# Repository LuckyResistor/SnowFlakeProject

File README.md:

# The Snowflake Decoration Project

This repository contains all hardware and software sources for the snowflake decoration project.
You will also find a number of documentation pages with the wiring or arrangement of the LEDs.

## More Information

Find more information about the project here:
[Snowflake Decoration Project](https://luckyresistor.me/projects/snow-flake-decoration/)

## License

All files are licensed under the GNU General Public License v3.0.

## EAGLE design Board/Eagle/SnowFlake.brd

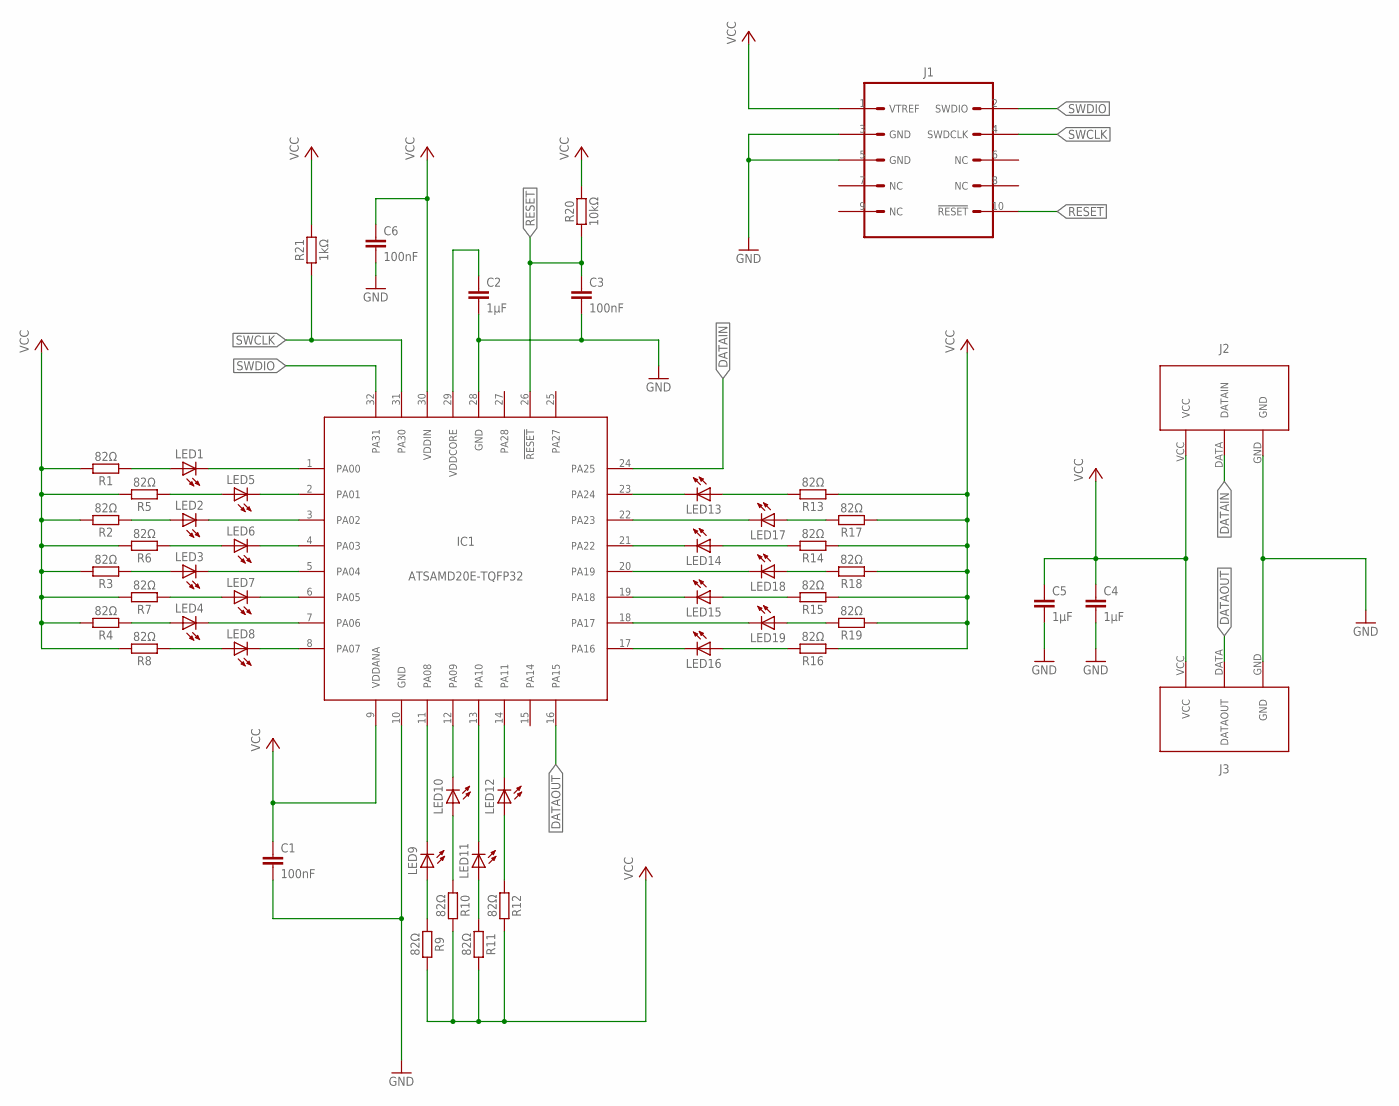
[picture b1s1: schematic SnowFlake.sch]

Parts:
C1, C3, C6: 100nF; CAPACITOR-0805-MURATA-GRM-21
C2, C4, C5: 1µF; CAPACITOR-0805-MURATA-GRM-21
IC1: ATSAMD20E-TQFP32; TQFP32-08
J1: CON-CORTEX-DEBUG-SMD1.27; CON-2X5-HARWIN-1.27
J2: CON-SNOWF-IN; CON-PADS-3XWIRE-B
J3: CON-SNOWF-OUT; CON-PADS-3XWIRE-T
LED1, LED2, LED3, LED4, LED5, LED6, LED7, LED8, LED9, LED10, LED11, LED12, LED13, LED14, LED15, LED16, LED17, LED18, LED19: LED0402; LED-0402-ROHM
R1, R2, R3, R4, R5, R6, R7, R8, R9, R10, R11, R12, R13, R14, R15, R16, R17, R18, R19: 82Ω; RESISTOR-0805-KOA-RK73-2A
R20: 10kΩ; RESISTOR-0805-KOA-RK73-2A
R21: 1kΩ; RESISTOR-0805-KOA-RK73-2A

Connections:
DATAIN: IC1.24 (PA25), J2.DATA (DATAIN)
DATAOUT: IC1.16 (PA15), J3.DATA (DATAOUT)
GND: C1.2, C2.2, C3.2, C4.2, C5.2, C6.2, IC1.10 (GND), IC1.28 (GND), J1.3 (GND), J1.5 (GND), J2.GND, J3.GND
LED1P: LED1.A, R1.1
LED1S: IC1.1 (PA00), LED1.C
LED2P: LED2.A, R2.1
LED2S: IC1.3 (PA02), LED2.C
LED3P: LED3.A, R3.1
LED3S: IC1.5 (PA04), LED3.C
LED4P: LED4.A, R4.1
LED4S: IC1.7 (PA06), LED4.C
LED5P: LED5.A, R5.1
LED5S: IC1.2 (PA01), LED5.C
LED6P: LED6.A, R6.1
LED6S: IC1.4 (PA03), LED6.C
LED7P: LED7.A, R7.1
LED7S: IC1.6 (PA05), LED7.C
LED8P: LED8.A, R8.1
LED8S: IC1.8 (PA07), LED8.C
LED9P: LED9.A, R9.1
LED9S: IC1.11 (PA08), LED9.C
LED10P: LED10.A, R10.1
LED10S: IC1.12 (PA09), LED10.C
LED11P: LED11.A, R11.1
LED11S: IC1.13 (PA10), LED11.C
LED12P: LED12.A, R12.1
LED12S: IC1.14 (PA11), LED12.C
LED13P: LED13.A, R13.2
LED13S: IC1.23 (PA24), LED13.C
LED14P: LED14.A, R14.2
LED14S: IC1.21 (PA22), LED14.C
LED15P: LED15.A, R15.2
LED15S: IC1.19 (PA18), LED15.C
LED16P: LED16.A, R16.2
LED16S: IC1.17 (PA16), LED16.C
LED17P: LED17.A, R17.2
LED17S: IC1.22 (PA23), LED17.C
LED18P: LED18.A, R18.2
LED18S: IC1.20 (PA19), LED18.C
LED19P: LED19.A, R19.2
LED19S: IC1.18 (PA17), LED19.C
RESET: C3.1, IC1.26 (!RESET), J1.10 (!RESET), R20.1
SWCLK: IC1.31 (PA30), J1.4 (SWDCLK), R21.1
SWDIO: IC1.32 (PA31), J1.2 (SWDIO)
VCC: C1.1, C4.1, C5.1, C6.1, IC1.9 (VDDANA), IC1.30 (VDDIN), J1.1 (VTREF), J2.VCC, J3.VCC, R1.2, R2.2, R3.2, R4.2, R5.2, R6.2, R7.2, R8.2, R9.2, R10.2, R11.2, R12.2, R13.1, R14.1, R15.1, R16.1, R17.1, R18.1, R19.1, R20.2, R21.2
VDDCORE: C2.1, IC1.29 (VDDCORE)

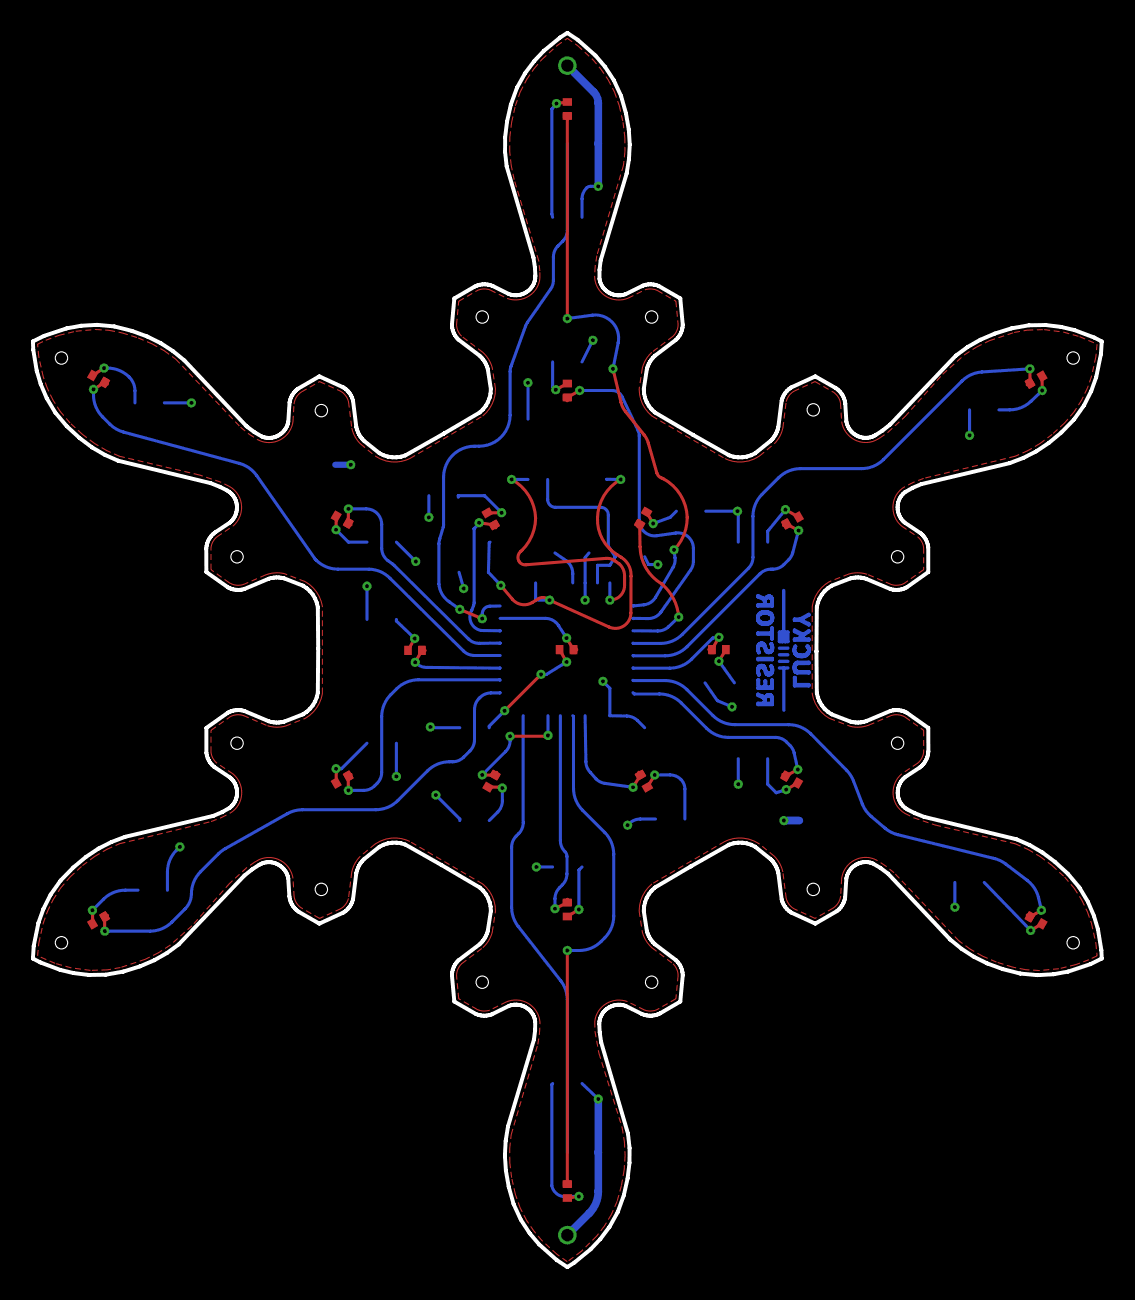
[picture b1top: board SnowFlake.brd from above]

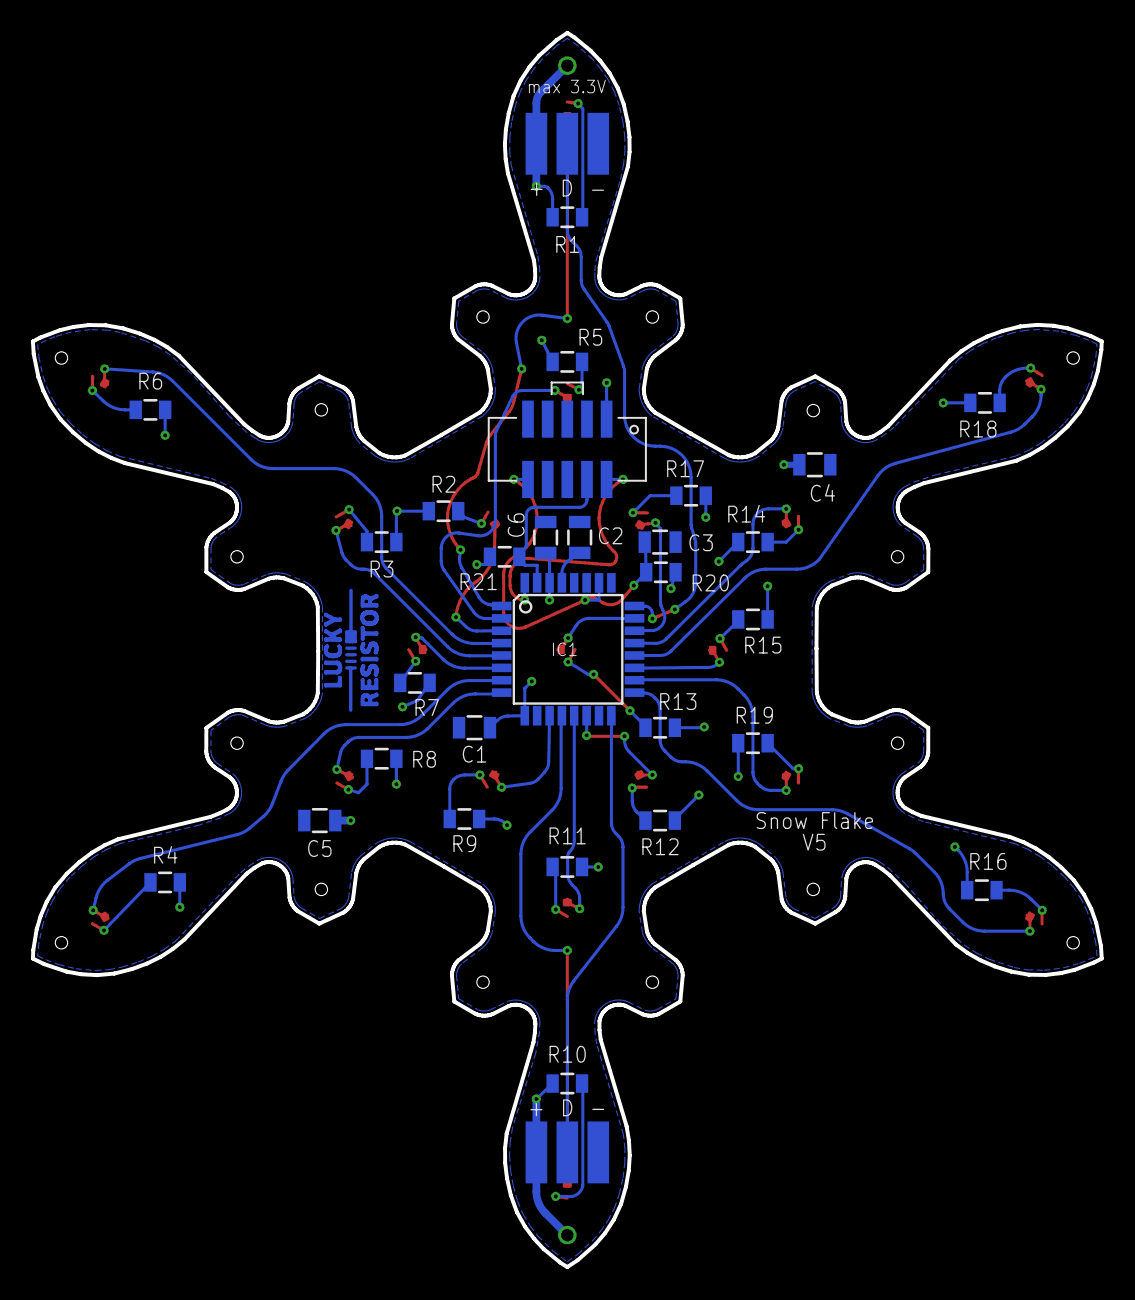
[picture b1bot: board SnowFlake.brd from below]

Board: 2 copper layers, 69.1 x 79.8 mm, 51 parts (32 on the bottom side), 46 nets.

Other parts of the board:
U$1: LR_LOGO_COPPER_8MM

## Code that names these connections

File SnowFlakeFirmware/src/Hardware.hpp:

//
// Snow Flake Project
// ---------------------------------------------------------------------------
// (c)2017 by Lucky Resistor. See LICENSE for details.
// https://luckyresistor.me
//
// This program is free software; you can redistribute it and/or modify
// it under the terms of the GNU General Public License as published by
// the Free Software Foundation; either version 2 of the License, or
// (at your option) any later version.
//
// This program is distributed in the hope that it will be useful,
// but WITHOUT ANY WARRANTY; without even the implied warranty of
// MERCHANTABILITY or FITNESS FOR A PARTICULAR PURPOSE.  See the
// GNU General Public License for more details.
//
// You should have received a copy of the GNU General Public License along
// with this program; if not, write to the Free Software Foundation, Inc.,
// 51 Franklin Street, Fifth Floor, Boston, MA 02110-1301 USA.
//
#pragma once


#include <cstdint>


/// The hardware abstraction layer.
///
namespace Hardware {


/// The port.
///
enum class PortName : uint8_t {
	PA00 = 0,
	PA01 = 1,
	PA02 = 2,
	PA03 = 3,
	PA04 = 4,
	PA05 = 5,
	PA06 = 6,
	PA07 = 7,
	PA08 = 8,
	PA09 = 9,
	PA10 = 10,
	PA11 = 11,
	PA14 = 14,
	PA15 = 15,
	PA16 = 16,
	PA17 = 17,
	PA18 = 18,
	PA19 = 19,
	PA22 = 22,
	PA23 = 23,
	PA24 = 24,
	PA25 = 25,
	PA27 = 27,
	PA28 = 28,
	PA30 = 30,
	PA31 = 31,
};


/// The multiplexing function.
///
enum class Multiplexing : uint8_t {
	Off, ///< Do not connect to any peripheral.
	A, ///< Connect to external interrupt.
	B, ///< Connect to analog input (REF, ADC, AC, PTC, DAC).
	C, ///< Connect to SERCOM.
	D, ///< Connect to SERCOM-ALT.
	E, ///< Connect to timer (TC).
	G, ///< Connect to COM.
	H, ///< Connect to Generic Clock.
};

/// Port Configuration.
///
enum class PortConfiguration : uint8_t {
	Disabled, ///< Remove the port from the GPIO (Hi-Z)
	Output, ///< Configure the port as output.
	Input, ///< Configure the port as input.
};

/// Pull up/down.
///
enum class PortPull : uint8_t {
	None, ///< Use no pull up/down resistor.
	Up, ///< Connect a pull up resistor.
	Down ///< Connect a pull down resistor.
};

/// The port state.
///
enum class PortState : uint8_t {
	Low, ///< Set the port to high state.
	High ///< Set the port to low state.
};


/// Initialize the MCU hardware.
///
void initialize();	


/// Set the basic port configuration.
///
void setPortConfiguration(PortName port, PortConfiguration configuration, PortPull pull = PortPull::None);

/// Set the peripheral multiplexing function for a pin.
///
void setPeripheralMultiplexing(PortName port, Multiplexing muxFunction);

/// Get the mask for a port.
///
constexpr uint32_t getMaskForPort(PortName port) {
	return (1UL << static_cast<uint8_t>(port));
}

/// Set the output for a port configured as output.
///
void setOutput(PortName port, PortState output);

/// Get the input state from a port configured as input.
///
PortState getInput(PortName port);

/// Get entropy for the pseudo random number generator
///
uint32_t getEntropy();

/// Set trace output A to high state.
///
void setTraceOutputA();

/// Set trace output A to low state.
///
void clearTraceOutputA();

/// Toggle trace output A.
///
void toggleTraceOutputA();

/// Set trace output B to high state.
///
void setTraceOutputB();

/// Set trace output B to low state.
///
void clearTraceOutputB();

/// Toggle trace output B
///
void toggleTraceOutputB();

	
}

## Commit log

2017-10-04 Initial in progress version.
2017-10-04 Working on the clock setup and adding access to the LED pins.
2017-10-04 Create an interrupt from TC0.
2017-10-05 First simple HAL layer with working LED PWM display and delay function.
2017-10-06 Adding boards, design and BOM to the project.
    Add missing gerber files for the bottom layer.
2017-10-07 Adding a initial version of the communication module.
    - Move specific hardware initialization into the display and communication module.
2017-10-09 Implemented initial scene management.
    - Renamed all header files with the suffix "hpp" to get the correct syntax highlighting in Atmel studio.
    - Changed linker option to use a size optimized library.
2017-10-09 Add the simple shift scene as a demo of the approach.
    - Add more functions to the pixel math module.
2017-10-18 Adding the Player class.
    - Adding a "chip.h" header to make switching the MCU simple for non studio builds.
    - Change the scene registry to allow storing in flash memory.
    - Prepare the ice sparkle scene (not implemented yet).
2017-10-21 Adding a fixed point data type for fast calculations.
    - Adding the new data type Fixed16 for very fast integer fixed point calculations.
    - Adding trace output configuration for timing measurements.
    - Converting the PixelMath functions into the new PixelValue data type.
2017-10-21 Adding a new scene using the new interpolating array.
2017-10-21 Add a simple rotation to blend between a few scenes.
2017-10-22 New random particle scene and display PWM code optimization.
    - Added a not yet finished random particle scene.
    - Optimized the display code to improve the very low LED levels. Make a smooth transition to off there.
2017-10-24 Fixing the initial state of the display after first optimization.
2017-10-24 Fixing the wait cycle to correctly wait for corase and fine tuning before switching to the new clock.
2017-10-24 Correcting the random counter class to get the particle effect working.
2017-10-24 Optimizing display performance by precalculating the PWM masks for all LEDs.
    - Optimizing the black to white transition with better timing.
2017-11-15 Working on the random scene transitions and other small improvements.
    - Adding a new simple diagonal scene.
    - Moving the used LED maps into a separate file to share them between scenes.
    - Add 8bit random numbers.
    - Add functions to get "hard" (no blend) and "smooth" (with blend) numbers from the array.
    - Fixing constants of the display module to optimize compilation.
    - Adding a (currently not working) random transition between scenes.
2017-11-15 Avoid infinite loop when repeated scene chosen
2017-11-15 Update the project to the latest CMSYS and DFP versions. Changing chip from SAMD20E15 to SAMD20E17.
    - Update to CMSYS 5.0.1
    - Update to SAMD20_DFP 1.2.91
    - Adding the LTO flag to the release build.
    - Changing the chip version from SAMD20E15 to SAMD20E17 as used on the final snow flake.
2017-11-18 Adding firmware binaries to the project.
2017-11-26 Create a final version of the "ice sparkle" scene.
    - Adding an offset to the RandomFrameCounters class to allow multiple instances with the same scene data block.
    - Create a module with shared value arrays.
    - Increase the index for the interpolating array to 16bit for larger arrays.
    - Adding the "ice sparkle" scene to the scene rotation.
    - Adding functions to the Frame class to multiple and add frames.
2017-11-26 Adding working debug binaries for the release.
2017-11-27 Adding new scene "Sky with Stars".
    - Fixing the project file for release builds.
    - Fix a minor problem in the IceSparke scene.
2017-11-28 Update the firmware binaries to match the latest changes.
    - Removed parameter to supress warning in build.
2017-11-30 Adding documentation about the communication protocol.
2017-11-30 Adding simple document about the idea of the deployment and how to connect the boards.
2017-12-03 Update the documentation with additional documents.
2017-12-03 Use the faster IOBUS to control the GPIO.
2017-12-03 Working on the communication component. Implementing the data send functionality and initial negotiaton.
    - Adding configuration functions to the HAL to configure ports in a visual way (slow but readable code).
    - Configure the timer and interrupt system to send the 32bit values and synchronization.
2017-12-09 Created a first working communication between the boards.
    - Refactored the code into more functions to make it readable.
    - Added a elapsed timer class to measure timeouts.
    - Added more global configuration options.
2017-12-09 Add new release builds with the latest changes.
2017-12-10 Use the communication to keep the scenes in the while stand in sync.
    - Update the binaries with the latest changes.
2017-12-26 Fixing the capacitor value in the schema from 10µF to 1µF.
2017-12-27 Adding the new scene "waves" to the firmware.
    - Adding entropy to the scenes and communicate it to other boards.
    - Adding a shifting map template class for shifting map calculations.
    - Fixing minor code issues with the `FrameIndex` type.
    - Removing the `Simple...` example scenes from the scene display for the production version.
    - Adding a map with rotation LED index mappings.
    - Adding new firmware binaries for this release.
2017-12-28 Creating the first release version for Winter 2017.
    - Adding sparkle to the `Waves` scene.
    - Adding the circles scene.
    - Minor timing adjustments.
    - Update the IceSparkle scene with the new `ShiftingMap`.
    - Adding the release binaries for this version.
2017-12-30 Fixes #5: Disable blending on the same scene if not wanted.
2017-12-30 Resolves #2: Reading some noisy values from the internal temperature sensor to generate a seed value for the PRNG.
2017-12-30 Increasing the communication pulse tolerance to fix some timing problems at the end of the strand.
2017-12-30 Update the binaries to this latest release.
2018-01-05 Adjusting the "Ice Sparkle" effect.
    - Lower base brightness.
    - Stronger sparkle effect.
    - Sparkle shift based on strand position.
2019-11-11 Add configuration and on/off via push button on the first data line.
2019-11-11 Turn all other platforms off while changing the configuration.
2019-11-11 Adding binary versions of the firmware for the SAMD20E15B chip.
2019-11-12 Adding a new scene "rain" to the firmware.
    - Fixing the duration values.
    - Adding a 4. auto program like the 1. with the additional rain scene.
2019-11-17 Removing race conditions in user input button handling.
    - Fix: Remove race condition by introducing a synchronized queue.
    - Cleanup: Moving the auto scene arrays into an own module to keep the application logic small.
2019-11-17 Adding firmware binaries for the latest version.
2019-11-18 Adding a README to the repository.
2019-11-21 Adding the push button to the connection diagram.
2019-12-05 Add a user scene to the firmware, which provides an easy start to program your own scenes.
2019-12-07 Removing code left from testing.
2020-07-06 Moving to a neutral terminology: primary/secondary.
    - No functional changes.
